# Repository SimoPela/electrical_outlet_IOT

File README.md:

# Electrical Outlet IoT

ESP32-based environmental monitoring firmware plus a lightweight web dashboard for live MQTT telemetry.

The project is built around an ESP32 running ESP-IDF/FreeRTOS, collecting indoor environment data from multiple sensors (air quality, climate, particulate matter, light spectrum, motion, gas, and audio level), then publishing JSON payloads to MQTT. A Node.js dashboard subscribes to these topics and visualizes live values and trends.

---

## Features

- Multi-sensor acquisition on I2C, UART, I2S, ADC, and GPIO.
- FreeRTOS architecture with dedicated acquisition, audio, system, and communication tasks.
- Shared mutex-protected runtime state (`g_device_state`) with validity/fault flags and timestamps.
- Wi-Fi station mode with automatic reconnect and MQTT telemetry publishing.
- System health evaluation and alarm logic (motion, gas threshold, CO2 level bands).
- Real-time web dashboard (Express + Socket.IO + Chart.js) driven by MQTT messages.

---

## Hardware and Sensors

### Controller
- ESP32 DevKit-style board (`platformio.ini`: `board = esp32dev`, framework `espidf`).

### Sensor set
- `SCD40`: CO2, temperature, humidity (I2C)
- `SHT41`: temperature, humidity (I2C)
- `SGP41`: VOC/NOx indices (I2C, optional compensation from SHT41)
- `BMP280`: pressure, temperature (I2C)
- `AS7341`: 8-channel visible spectrum (I2C)
- `PMS7003`: PM1.0 / PM2.5 / PM10 (UART)
- `MiCS-5524`: gas raw voltage + estimated ppm (ADC)
- `AS312`: PIR motion sensor (GPIO)
- `INMP441`: noise level estimate in dB SPL (I2S)
- RGB status LED (GPIO)

### Default pinout
Defined in `lib/config/include/esp32_pinout.h`:

- I2C SDA/SCL: GPIO `21` / `22`
- PMS7003 TX/RX (sensor side): GPIO `16` / `17`
- PMS7003 SET/RESET: GPIO `4` / `5`
- PIR output: GPIO `27`
- I2S WS/SCK/SD: GPIO `25` / `26` / `33`
- MiCS-5524 ADC: GPIO `34`
- RGB LED R/G/B: GPIO `13` / `12` / `14`

---

## Firmware Architecture

### Boot flow
`app_main()` in `src/main.c` performs:

1. `device_state_init()`
2. `sensor_init_all()`
3. `network_app_init()` and wait for Wi-Fi connection
4. `mqtt_app_start()`
5. Task creation: `acquisition_task`, `audio_task`, `comm_task`, `system_task`

If sensor/network init fails, startup aborts.

### FreeRTOS tasks
Task definitions are configured in `include/task_config.h`.

| Task | Main role | Priority | Stack (words) | Loop period |
|---|---|---:|---:|---:|
| `acquisition_task` | Poll environmental sensors and update shared state | 2 | 4096 | 1000 ms |
| `audio_task` | Read INMP441 and update noise metrics | 2 | 4096 | 500 ms |
| `comm_task` | Publish MQTT system/environment/alarm payloads | 3 | 4096 | 100 ms |
| `system_task` | Evaluate health and alarm state | 4 | 4096 | 100 ms |

The firmware uses periodic polling instead of interrupt-driven sampling for most sensors.
`acquisition_task` runs every 1000 ms and checks per-sensor deadlines (for example 1000 ms, 2000 ms, 2500 ms, 5000 ms depending on the sensor). When a deadline is reached, it reads that sensor, updates local values, then commits a synchronized snapshot to the shared device state.
In parallel, `audio_task` handles the INMP441 capture pipeline at its own cadence, while `system_task` computes health/alarm flags and `comm_task` publishes MQTT payloads from a consistent state snapshot.

```mermaid
flowchart LR
    subgraph RTOS[FreeRTOS Runtime]
        ACQ["acquisition_task (1000 ms loop)\n- deadline-based polling\n- multi-sensor reads"]
        AUD["audio_task (500 ms loop)\n- INMP441 read\n- noise_db update"]
        SYS["system_task (100 ms loop)\n- health checks\n- alarm logic"]
        COM["comm_task (100 ms loop)\n- MQTT publish scheduler"]
    end

    DS[("g_device_state\n(mutex-protected shared snapshot)")]
    BRK["MQTT broker"]

    ACQ -->|"poll sensors + write measurements"| DS
    AUD -->|"write audio metrics"| DS
    SYS <-->|"read/write system flags"| DS
    COM -->|"read snapshot"| DS
    COM -->|"publish JSON payloads"| BRK
```

### Shared runtime state
`lib/device_state/include/device_state.h` defines:

- `g_device_state` (`device_state_t`): all sensor values, validity/fault flags, timestamps, connectivity flags, alarm status.
- `g_device_state_mutex`: protects shared state access.
- `g_sensor_driver_mutex`: serializes sensor driver access and restore operations.

### Health and alarms
Implemented in:
- `lib/health/src/health.c`
- `lib/alarm/src/alarm.c`

Current logic includes:
- degraded mode/system status based on validity/fault/freshness checks,
- motion alarm from PIR,
- gas alarm when MiCS-5524 estimated ppm is above threshold,
- CO2 qualitative level (`optimal`, `good`, `moderate`, `poor`, `very poor`, `critical`).

---

## MQTT Interface

Topic builders are implemented in `lib/mqtt/src/mqtt_topic.c`.

Published topics:

- `devices/<device_id>/telemetry/environment`
- `devices/<device_id>/status/system`
- `devices/<device_id>/event/alarm`

Payload builders are in `lib/mqtt/src/mqtt_payload.c`:

- **Environment payload**: CO2, temperatures, humidities, pressure, VOC/NOx, PM values, light channels, gas values, noise dB.
- **System payload**: `system_ok`, `degraded_mode`, `wifi_connected`, `mqtt_connected`, `status`.
- **Alarm payload**: `as312_alarm`, `mics5524_alarm`, `co2_alarm_level`.

---

## Repository Structure

```text
.
├── src/                    # app_main and FreeRTOS task implementations
├── include/                # task headers and timing/priority configuration
├── lib/
│   ├── config/             # app config template and ESP32 pin mapping
│   ├── sensor_init/        # centralized peripheral/sensor initialization
│   ├── device_state/       # shared state and mutexes
│   ├── network/            # Wi-Fi connection management
│   ├── mqtt/               # topic/payload/publish/client logic
│   ├── health/             # system health checks
│   ├── alarm/              # alarm decision logic
│   ├── inmp441/            # audio wrapper and dB estimate
│   └── ...                 # individual sensor drivers
├── server/                 # Node.js + Socket.IO live dashboard
├── scripts/                # build helper scripts (clangd/toolchain patching)
├── datasheet/              # sensor datasheets
└── platformio.ini          # PlatformIO environment
```

---

## Getting Started

### 1) Firmware (ESP32)

### Prerequisites
- [PlatformIO Core](https://platformio.org/install)
- ESP32 board connected over USB

### Configuration
1. Create/update `lib/config/include/app_config.h` using `lib/config/include/app_config_template.h`.
2. Set:
   - `APP_WIFI_SSID`
   - `APP_WIFI_PASSWORD`
   - `APP_MQTT_BROKER_URI`
   - `APP_MQTT_USERNAME`
   - `APP_MQTT_PASSWORD`
   - `APP_DEVICE_ID`
3. If needed, adjust GPIO mapping in `lib/config/include/esp32_pinout.h`.
4. Update serial upload settings in `platformio.ini` (`upload_port`, optionally `upload_speed`).

### Build, flash, monitor
```bash
pio run
pio run -t upload
pio device monitor -b 115200
```

Other useful commands:
```bash
# clean build
pio run -t clean
# erase flash
pio run -t erase
# generate compiledb database for IDE indexing
pio run -t compiledb
```

### 2) Dashboard server

The dashboard is located in `server/` and subscribes to MQTT topics, then forwards updates to browser clients via Socket.IO.

### Prerequisites
- Node.js 18+ recommended

### Setup
```bash
cd server
npm install
cp .env.example .env
```

Edit `.env`:
- `MQTT_BROKER_URL`
- `MQTT_USERNAME`
- `MQTT_PASSWORD`
- `PORT` (default `3000`)
- `ALARM_ON_MS` (temporary alarm display duration)

### Run
```bash
npm start
```

Open: `http://localhost:3000`

---

## Development Notes

- Build options and monitor/upload defaults are in `platformio.ini`.
- `scripts/update_clangd_toolchain.py` updates `.clangd` include sections after build for better IDE indexing.
- Sensor polling and publish intervals are centralized in `include/task_config.h`.
- Debug logs use ESP-IDF logging macros (`ESP_LOGE/W/I/D`).

---

## Security Notes

- Do not commit real Wi-Fi/MQTT credentials.
- Keep secrets only in local config files (`app_config.h`, `server/.env`) and exclude them from public history.

---

## License

This project is licensed under the Apache License 2.0 (see source headers).

## Authors

- Simone Pelascini
- Aurélien Bollin

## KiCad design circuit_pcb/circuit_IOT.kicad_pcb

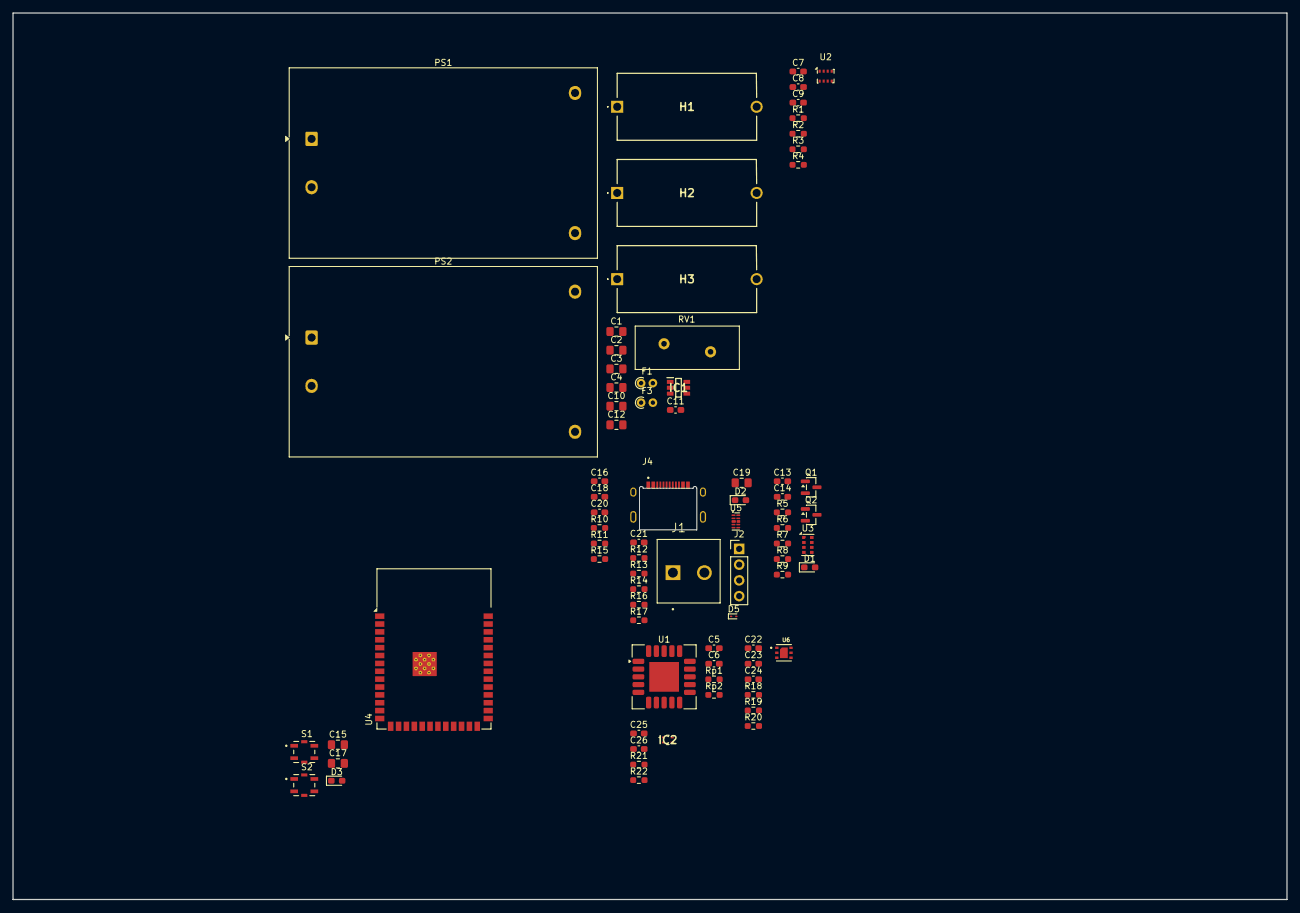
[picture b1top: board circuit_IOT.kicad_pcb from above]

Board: 2 copper layers, 205.5 x 143.0 mm, 77 parts (0 on the bottom side), 36 nets, no tracks yet.

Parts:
C1, C2, C10, C12, C17, C19: 10uF; C_0805_2012Metric_Pad1.18x1.45mm_HandSolder
C3, C4, C15: 22uF; C_0805_2012Metric_Pad1.18x1.45mm_HandSolder
C5, C7, C8, C13, C16, C20, C21, C24, C26: 100nF; C_0603_1608Metric_Pad1.08x0.95mm_HandSolder
C6, C9, C14, C18, C22, C23, C25: 1uF; C_0603_1608Metric_Pad1.08x0.95mm_HandSolder
C11: 10uF; C_0603_1608Metric_Pad1.08x0.95mm_HandSolder
D1, D2, D3: LED; D_0603_1608Metric_Pad1.05x0.95mm_HandSolder
D5: SZESD9B5.0ST5G; D_SOD-923
F1: Fuse: Thermal Fuse 3.3V module; R_Axial_DIN0204_L3.6mm_D1.6mm_P1.90mm_Vertical
F3: Fuse: Thermal Fuse 5V module; R_Axial_DIN0204_L3.6mm_D1.6mm_P1.90mm_Vertical
H1, H2, H3: 0031.8201.G; 00318201G
IC1: AP7312-1833W6-7; SOP95P285X145-6N
IC2: SHT41A-AW1B-R2; SHT41AAW1BR2
J1: TB007-508-02BE; CUI_TB007-508-02BE
J2: Conn_01x04; PinHeader_1x04_P2.54mm_Vertical
J4: UJ20-C-H-G-MSMT-4-P16-TR; SAMESKY_UJ20-C-H-G-MSMT-4-P16-TR
PS1: HLK-10M05; Converter_ACDC_Hi-Link_HLK-10Mxx
PS2: HLK-10M03; Converter_ACDC_Hi-Link_HLK-10Mxx
Q1, Q2: BSS138; SOT-23
R1, R2, R3, R4, R5, R6, R7, R8, R9, R11, R19, R20, R21, R22: 10K; R_0603_1608Metric_Pad0.98x0.95mm_HandSolder
R10, R12, R13: 5.1K; R_0603_1608Metric_Pad0.98x0.95mm_HandSolder
R14, R15: 5K; R_0603_1608Metric_Pad0.98x0.95mm_HandSolder
R16, R17: 22; R_0603_1608Metric_Pad0.98x0.95mm_HandSolder
R18: 4.7; R_0603_1608Metric_Pad0.98x0.95mm_HandSolder
RV1: Varistor; RV_Disc_D16.5mm_W6.7mm_P7.5mm
Rp1, Rp2: 10K; R_0603_1608Metric_Pad0.98x0.95mm_HandSolder
S1, S2: TS21-34-035-BK-260-SMT-TR; SW_TS21-34-035-BK-260-SMT-TR
U1: SCD40-D-R2; Sensirion_SCD4x-1EP_10.1x10.1mm_P1.25mm_EP4.8x4.8mm
U2: BMP280; Bosch_LGA-8_2x2.5mm_P0.65mm_ClockwisePinNumbering
U3: AS7341DLG; AMS_OLGA-8_2x3.1mm_P0.8mm
U4: ESP32-S3-WROOM-1
U5: D3V3XA4B10LP; Diodes_UDFN-10_1x2.5mm_P0.5mm
U6: SGP41-D-R4; XDCR_SGP41-D-R4

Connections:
1.8V: C12.1, C13.1, C14.1, IC1.6 (OUT1), Q1.1 (G), Q2.1 (G), R8.1, R9.1, U3.1 (VDD)
3.3V: C2.1, C4.1, C5.1, C6.1, C7.1, C8.1, C9.1, C10.1, C15.1, C16.1, C17.1, C23.1, C24.1, C25.1, C26.1, D1.2 (A), H3.2, IC1.3 (EN2), IC1.4 (EN1), IC1.5 (IN), IC2.3 (VDD), J2.3, R2.1, R3.1, R4.1, R5.1, R6.1, R7.1, R10.1, R11.1, R15.1, R18.1, R19.1, R20.1, R21.1, R22.1, Rp1.1, Rp2.1, U1.7 (VDD), U1.19 (VDD), U2.6 (VDDIO), U2.8 (VDD), U4.2 (3V3), U6.5 (VDDH)
5V: C1.1, C3.1, H2.2
AP3.3V: C11.1, IC1.1 (OUT2)
BOOT: S2.2, U4.27 (IO0)
CSB_BMP280: R3.2, U2.2 (CSB)
D+: R17.2, U4.14 (USB_D+), U5.1, U5.10 (NC)
D-: R16.2, U4.13 (USB_D-), U5.2, U5.9 (NC)
EN: S1.2, U4.3 (EN)
GND: C1.2, C2.2, C3.2, C4.2, C5.2, C6.2, C7.2, C8.2, C9.2, C10.2, C11.2, C12.2, C13.2, C14.2, C15.2, C16.2, C17.2, C18.2, C19.2, C20.2, C21.2, C22.2, C23.2, C24.2, C25.2, C26.2, D2.1 (K), D3.1 (K), D5.1 (A1), IC1.2 (GND), IC2.4 (VSS), J2.4, J4.A1_B12 (GND), J4.B1_A12 (GND), J4.SH1 (SHIELD), J4.SH2 (SHIELD), J4.SH3 (SHIELD), J4.SH4 (SHIELD), PS1.3 (-Vout), PS2.3 (-Vout), R1.2, R12.2, R13.2, S1.3, S1.4, S2.3, S2.4, U1.6 (GND), U1.20 (GND), U1.21 (GND), U2.1 (GND), U2.7 (GND), U3.3 (GND), U3.5 (PGND), U4.1 (GND), U4.40 (GND), U4.41 (GND), U5.3 (VSS), U5.8 (VSS), U6.2 (VSS), U6.4 (N/A), U6.7 (EXP)
L_230V: J1.1, PS1.1 (AC/L), PS2.1 (AC/L), RV1.1
N_230V: H1.2, J1.2
unnamed: C18.1, R11.2, S1.1
unnamed: C20.1, R10.2, S2.1
unnamed: D1.1 (K), U3.4 (LDR)
unnamed: D2.2 (A), R14.2
unnamed: D3.2 (A), R15.2
unnamed: F1.1, F3.2
unnamed: F3.1, H1.1
unnamed: J4.A5 (CC1), R13.1
unnamed: J4.B5 (CC2), R12.1
unnamed: J4.A7 (DN1), J4.B7 (DN2), R16.1
unnamed: J4.A6 (DP1), J4.B6 (DP2), R17.1
unnamed: H2.1, PS1.4 (+Vout)
unnamed: F1.2, PS1.2 (AC/N), PS2.2 (AC/N), RV1.2
unnamed: H3.1, PS2.4 (+Vout)
unnamed: R5.2, U3.7 (INT)
unnamed: C22.1, R18.2, U6.1 (VDD)
RXD0: J2.2, U4.36 (RXD0)
SCL: IC2.2 (SCL), Q2.2 (S), R2.2, R6.2, R20.2, R21.2, Rp1.2, U1.9 (SCL), U2.4 (SCK), U6.6 (SCL)
SCL18_AS7341: Q2.3 (D), R9.2, U3.2 (SCL)
SDA: IC2.1 (SDA), Q1.2 (S), R4.2, R7.2, R19.2, R22.2, Rp2.2, U1.10 (SDA), U2.3 (SDI), U6.3 (SDA)
SDA18_AS7341: Q1.3 (D), R8.2, U3.8 (SDA)
SDO_BMP280: R1.1, U2.5 (SDO)
TXD0: J2.1, U4.37 (TXD0)
VBUS: C19.1, C21.1, D5.2 (A2), J4.A4_B9 (VBUS), J4.B4_A9 (VBUS), R14.1

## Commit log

2026-03-05 [new] master: first commit
2026-03-05 [new] work: first commit, added readme.md
2026-03-05 [new] work: new readme.md and checklist of components required for the first prototype
2026-03-05 [new] work: added T13 size in readme.md, only as information
2026-03-09 [new] readme.md: new lines of description
2026-03-09 [new] main.c: delete mq7 sensor
2026-03-09 [new] readme.md: v1.0 mermaid layout of prototype
2026-03-09 [new] readme.md: v1.1 mermaid layout of prototype
2026-03-09 [new] readme.md: v1.2 mermaid layout of prototype
2026-03-09 [new] readme.md: v1.3 mermaid layout of prototype
2026-03-09 [new] readme.md: v1.4 mermaid layout of prototype
2026-03-09 [new] readme.md: new paragraph
2026-03-09 [new] readme.md: new chapitre
2026-03-09 [new] readme.md: correction of errors in readme
2026-03-09 [new] circuit pcb: added PMS7003
2026-03-09 [new] readme.md: added led rgb status
2026-03-10 [new] clean all the project and I've prepared all the folders
2026-03-10 [new] envirement for coding ready
2026-03-10 [new] datasheet: add some datasheet
2026-03-11 [new] include: cleaned this folder
2026-03-11 [new] src/include: added task files
2026-03-11 [new] src: added funtion to control stack usage of each task
2026-03-11 [new] device_state: new file with mutex and global structure
2026-03-11 [new] acqu_state: add an example of sub scheduler
2026-03-11 [new] readme: add example diagram for as312
2026-03-11 [new] task_acq: updated with only one access to the mutex, less overhead
2026-03-11 [new] system task: added motion and readme with examples
2026-03-11 [new] mqtt_payload: new files in lib/
2026-03-13 [new] mqtt: modify some files and create payload handler
2026-03-13 [debug] mqtt: fix some bug in comm.c and payload.c
2026-03-13 [new] readme: layout correct
2026-03-17 [new] licence: added Apache 2.0
2026-03-17 [new] readme: in progress
2026-03-18 [new] topic: new topic builder
2026-03-18 [new] mqtt publish: first version of publisher
2026-03-18 [new] publisher: fix some bug
2026-03-18 [new] comm and app: new file and integration
2026-03-18 [new] network: integrated in code and corrected some bug
2026-03-18 [new] config: added securised config file and template
2026-03-18 [flag] copyright added to new files
2026-03-18 [new] gitignore: added prototype of latex raport
2026-03-18 [new] task: macro for task interval
2026-03-18 [new] components: new description
2026-03-19 [new] test esp32 + server -> work
2026-03-19 [new] csv component updated with pinout
2026-03-20 [new] pinout updated
2026-03-20 [new] sensor init: new files
2026-03-20 [new] as312: new files
2026-03-21 [new] micd5524: v1.2 adc and calibration
2026-03-21 [new] new folder herarchy inside lib
2026-03-21 [new] script header updated
2026-03-21 [new] scd40 try to fix bug
2026-03-21 [bug] bug in scd40 drivers
2026-03-23 [new] added external components
2026-03-23 [new] new wrapper for scd40, sht41 and sgp41
2026-03-23 [new] added bmp280 wrapper
2026-03-23 "[new] fix bug"
2026-03-23 [new] new scd40 wrapper, with external component
2026-03-23 [new] as7341 wrapper added, v1.0
2026-03-23 [new] update component pinout
2026-03-23 [new] pinout esp32 updated
2026-03-23 [new] fix scd40 and add new pinout for pms7003
2026-03-23 [new] pms7003 driver added and works
2026-03-23 [new] all sensors in acquisition task work
2026-03-24 [new] first version of drivers for inmp441
2026-03-24 [new] files header updated and also new readme
2026-03-24 [new] add doxygen comments
2026-03-24 [new] readme updated
2026-03-24 [debug] add new system of debuging
2026-03-24 [new] healt system implemented
2026-03-24 [BUG] new system of restore, introduce a bug!
2026-03-26 [bug] still have a bug in healt restore
2026-03-30 [new] restore fixed
2026-03-30 [new] restore completed
2026-03-31 [new] alarm logic
2026-03-31 [new] mqtt test
2026-03-31 ignore local app_config.h
2026-03-31 [fix] error credentials
2026-03-31 [new] server dashboard
2026-04-24 [new] system updated
2026-04-26 [new] update task parameter
2026-04-26 [new] raport added
2026-04-26 [bug] readme updated
2026-04-26 [new] external file

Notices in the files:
README.md:
License: Apache 2.0
